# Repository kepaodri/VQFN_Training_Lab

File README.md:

# VQFN_Training_Lab
PCB Design for a VQFN and DFN package soldering practice board using an LDO regulator.
The purpose of this project is to give different hobbyists without prior experience with this type of package the opportunity to perform soldering tests to reach a good level of mastery. Soldering can be done for example using both reflow hot plate and/or hot air gun. 

## Project Description
This project features a power supply circuit centered on the AP7361C (DFN) LDO regulator. It converts a 2.2V to 6.0V input into a stable 3.3V output with ±1% accuracy. To manage power, SW1 (POWER ON) and SW2 (RESET) pulses are debounced by a 74LVC2G14 Schmitt-Trigger inverter (TSSOP6). A 74AHCT32 (VQFN) OR gate creates a latch, while a 74HCT08 (VQFN) AND gate acts as a kill switch to maintain Enable signal only if the latch is active and RESET is not pressed. 2 green LEDs (D1, D2) provide visual feedback status for the +5V and +3V3 rails.

### Hardware Features
- Input Voltage Range: 2.2V - 6V
- Output Voltage: 3.3V Fixed
- Output voltage accuracy: +-1%
- Max Current: 1.5A

### PCB Features
- Layers: 2
- Thickness: 1.6mm
- Width: 45mm
- Heigth: 50mm

### 3D Render

## Tools Used
KiCad: 9.0.4

## Licensing and Open Source Hardware
This project is certified as \*\*Open Source Hardware\*\*. 

### Hardware License
The hardware design files are licensed under the \*\*CERN Open Hardware Licence Version 2 - Permissive (CERN-OHL-P-2.0)\*\*. 
> You may redistribute and modify this documentation and build products based on it under the terms of the CERN-OHL-P v2.0.
### Documentation License
All associated documentation, including manuals and images, is licensed under \*\*Creative Commons Attribution-ShareAlike 4.0 International (CC BY-SA 4.0)\*\*.

## Disclaimer
\*\*This design is provided "AS-IS" without any express or implied warranties.\*\* The author is not responsible for any damage to equipment, fire, or personal injury resulting from the assembly or use of this PCB.

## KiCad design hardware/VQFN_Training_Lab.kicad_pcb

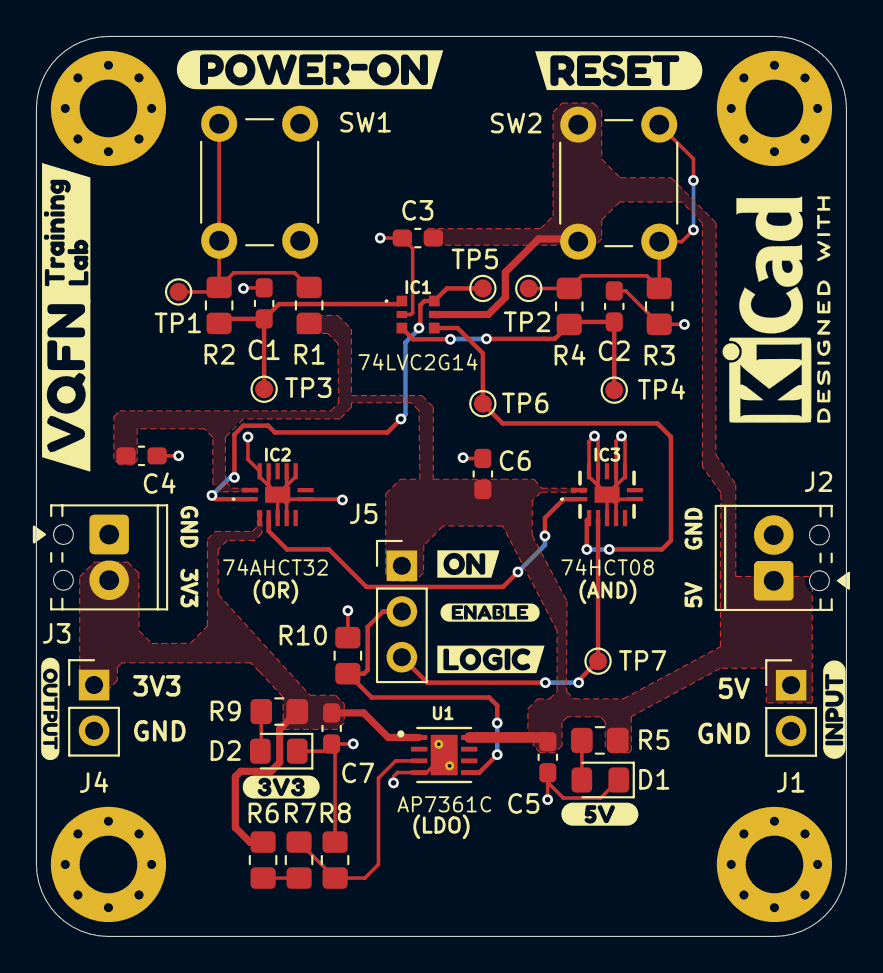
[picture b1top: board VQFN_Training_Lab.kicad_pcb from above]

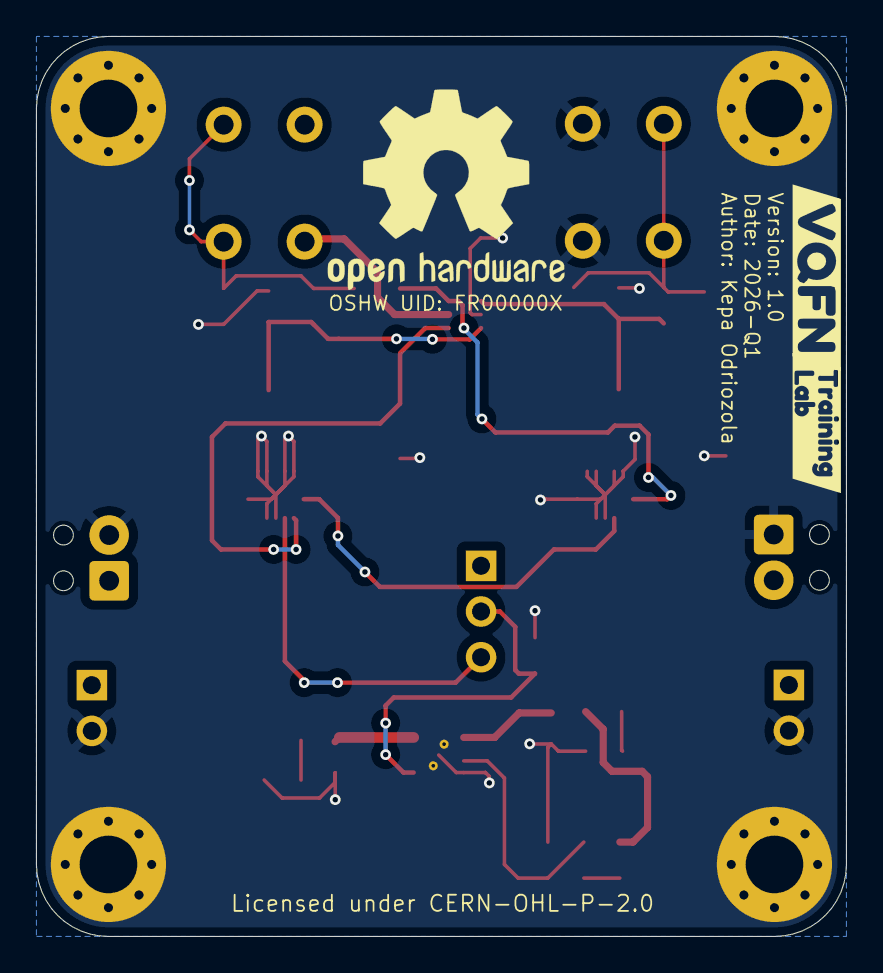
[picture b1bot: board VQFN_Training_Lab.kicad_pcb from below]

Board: 2 copper layers, 45.0 x 50.0 mm, 54 parts (2 on the bottom side), 16 nets.

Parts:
C1, C2, C3, C4, C6: 100n/25V/0603; C_0603_1608Metric_Pad1.08x0.95mm_HandSolder
C5, C7: 4u7/16V/0603; C_0603_1608Metric_Pad1.08x0.95mm_HandSolder
D1, D2: LED; LED_0805_2012Metric_Pad1.15x1.40mm_HandSolder
H1, H2, H3, H4: MountingHole_Pad; MountingHole_3.2mm_M3_Pad_Via
IC1: 74LVC2G14GW,125; 74LVC2G14GW125
IC2: 74AHCT32BQ,115; 74AHCT32BQ115
IC3: 74HCT08BQ,115; 74HCT08BQ115
J1, J4: Conn_01x02_Pin; PinHeader_1x02_P2.54mm_Vertical
J2, J3: Screw_Terminal_01x02; TerminalBlock_Phoenix_MPT-0,5-2-2.54_1x02_P2.54mm_Horizontal
J5: Conn_01x03_Pin; PinHeader_1x03_P2.54mm_Vertical
R1, R3, R6, R10: 10K/1%; R_0805_2012Metric_Pad1.20x1.40mm_HandSolder
R2, R4: 1K/1%; R_0805_2012Metric_Pad1.20x1.40mm_HandSolder
R5: 200/1%; R_0805_2012Metric_Pad1.20x1.40mm_HandSolder
R7, R8: 4K7/1%; R_0805_2012Metric_Pad1.20x1.40mm_HandSolder
R9: 30/1%; R_0805_2012Metric_Pad1.20x1.40mm_HandSolder
SW1, SW2: SW_Push; SW_PUSH_6mm_H5mm
TP1, TP2, TP3, TP4, TP5, TP6, TP7: TestPoint; TestPoint_Pad_D1.0mm
U1: AP7361C-FGE-7; SON65P300X300X63-9N
kibuzzard-695A7D8B: G***; kibuzzard-695A7D8B
kibuzzard-695A7DB0: G***; kibuzzard-695A7DB0
kibuzzard-695A7DF5: G***; kibuzzard-695A7DF5
kibuzzard-695A7F36: G***; kibuzzard-695A7F36
kibuzzard-695A7F50: G***; kibuzzard-695A7F50
kibuzzard-695C2DAE, kibuzzard-695C2DAE#2: G***; kibuzzard-695C2DAE
kibuzzard-695C2DD0, kibuzzard-695C2DD0#2: G***; kibuzzard-695C2DD0
kibuzzard-695C241E: G***; kibuzzard-695C241E
kibuzzard-695C2423: G***; kibuzzard-695C2423
kibuzzard-696FF104: G***; kibuzzard-696FF104
kibuzzard-696FF158: G***; kibuzzard-696FF158

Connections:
+3V3: C7.1, IC2.2 (1B), J3.2, J4.1, R6.1, R9.1, U1.1 (OUT)
+5V: C3.1, C4.1, C5.1, C6.1, IC1.5 (VCC), IC2.14 (VCC), IC3.14 (VCC), J1.1, J2.1, J5.1, R1.1, R5.1, SW2.2, U1.8 (IN)
/LDO_EN: IC3.3 (1Y), J5.3, TP7.1
/LDO_EN_SEL: J5.2, R10.1, U1.5 (EN)
/POWER_ON: C1.1, IC1.1 (1A), R2.2, TP3.1
/RESET: C2.1, IC1.3 (2A), R4.2, TP4.1
GND: C1.2, C2.2, C3.2, C4.2, C5.2, C6.2, C7.2, D1.1 (K), D2.1 (K), H1.1, H2.1, H3.1, H4.1, IC1.2 (GND), IC2.4 (2A), IC2.5 (2B), IC2.7 (GND_1), IC2.9 (3A), IC2.10 (3B), IC2.12 (4A), IC2.13 (4B), IC2.15 (GND_2), IC3.4 (2A), IC3.5 (2B), IC3.7 (GND_1), IC3.9 (3A), IC3.10 (3B), IC3.12 (4A), IC3.13 (4B), IC3.15 (GND_2), J1.2, J2.2, J3.1, J4.2, R3.2, R8.2, R10.2, SW1.1, U1.4 (GND), U1.9 (GND), U1.10, U1.11
unnamed: D1.2 (A), R5.2
unnamed: D2.2 (A), R9.2
unnamed: IC1.6 (1Y), IC2.1 (1A), TP5.1
unnamed: IC1.4 (2Y), IC3.2 (1B), TP6.1
unnamed: IC2.3 (1Y), IC3.1 (1A)
unnamed: R1.2, R2.1, SW1.2, TP1.1
unnamed: R3.1, R4.1, SW2.1, TP2.1
unnamed: R6.2, R7.1
unnamed: R7.2, R8.1, U1.3 (ADJ/NC)

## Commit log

2026-01-25 Added gerber and drill files
2026-01-25 Update README.md
    Added PCB features
2026-01-25 Added KiCad project files
2026-01-25 Added "doc" folder
    Contains Schematic and Datasheet files
2026-01-29 Update README.md
    Modified main description of project. Added few details about purpose
2026-02-05 Delete renders/VQFN_Training_Lab_bottomRayTracing.png
    Update must be done with OSHW UID
2026-02-05 Delete renders/VQFN_Training_Lab_bottom.png
    Update must be done with OSHW UID
2026-02-05 Update with OSHW UID

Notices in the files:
hardware/VQFN_Training_Lab.kicad_pcb:
Licensed under CERN-OHL-P-2.0
